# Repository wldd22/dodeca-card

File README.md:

# Dodeca Card

A stylised business card with segmented displays and a capacitive slider.

## Details
PCB made in **KiCad**<br>
Firmware uses **CircuitPython**

**Components**:
- **Seeed Studio XIAO ESP32S3**: Microcontroller
- **MAX7219-HLF-5V**: Display Driver IC
- **0.56 inch 4 Digit 7 Segment Display**: Segmented displays
- **MCMF006FF3002A50**: Through Hole Resistor

**Features**:
- **8 seven-segment digits**, in two sets, connected via a MAX7219 driver
- 8 step **capacitive touch** slider

## About
This project, inspired by [Mitxela's StyloCard](https://mitxela.com/projects/stylocard),
was originally made for week 4 (Display week) of Hack Club's Half Life. I wanted to make
a compact board with stylised graphics on it and a simple display that could show live
values or text updating, like a countdown, an RSS feed, or Github stars.

The touch slider at the bottom of the board acts as a multi-purpose input. It can be used
to scroll through text, select/change options, or adjust values smoothly. It has 8 steps,
corresponding to the 8 digits on the display, meaning it can also be used to individually
target digits on the display.

## Images

### Schematic

### PCB Routing

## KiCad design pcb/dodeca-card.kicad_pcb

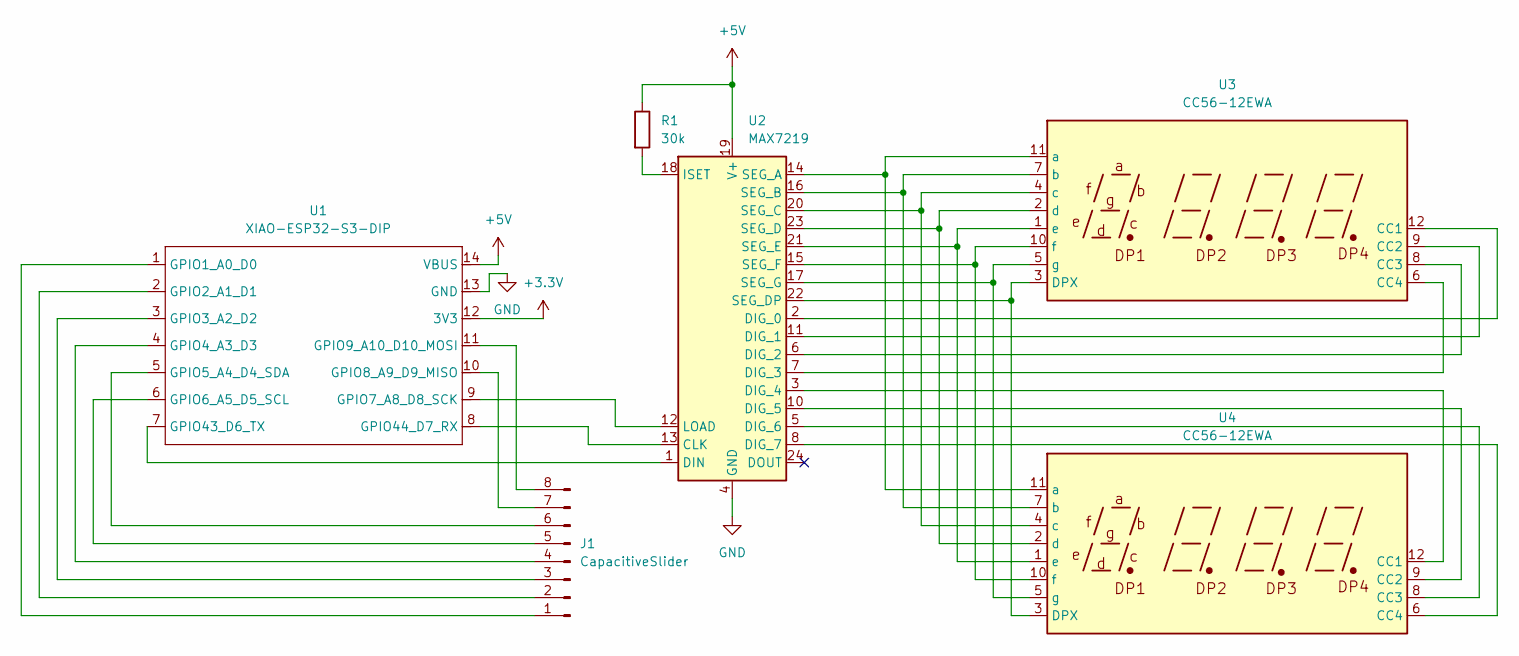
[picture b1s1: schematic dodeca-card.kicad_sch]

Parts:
J1: CapacitiveSlider; TouchSlider-8
R1: 30k; R_Axial_DIN0207_L6.3mm_D2.5mm_P10.16mm_Horizontal
U1: XIAO-ESP32-S3-DIP
U2: MAX7219; DIP-24_W15.24mm
U3, U4: CC56-12EWA; CA56-12EWA

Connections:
+3.3V: U1.12 (3V3)
+5V: R1.1, U1.14 (VBUS), U2.19 (V+)
GND: U1.13 (GND), U2.4 (GND), U2.9 (GND)
unnamed: J1.1, U1.1 (GPIO1_A0_D0)
unnamed: J1.2, U1.2 (GPIO2_A1_D1)
unnamed: J1.3, U1.3 (GPIO3_A2_D2)
unnamed: J1.4, U1.4 (GPIO4_A3_D3)
unnamed: J1.5, U1.6 (GPIO6_A5_D5_SCL)
unnamed: J1.6, U1.5 (GPIO5_A4_D4_SDA)
unnamed: J1.7, U1.10 (GPIO8_A9_D9_MISO)
unnamed: J1.8, U1.11 (GPIO9_A10_D10_MOSI)
unnamed: U1.9 (GPIO7_A8_D8_SCK), U2.12 (LOAD)
unnamed: U1.7 (GPIO43_D6_TX), U2.1 (DIN)
unnamed: U1.8 (GPIO44_D7_RX), U2.13 (CLK)
unnamed: U2.2 (DIG_0), U3.12 (CC1)
unnamed: U2.11 (DIG_1), U3.9 (CC2)
unnamed: U2.6 (DIG_2), U3.8 (CC3)
unnamed: U2.7 (DIG_3), U3.6 (CC4)
unnamed: U2.3 (DIG_4), U4.12 (CC1)
unnamed: U2.10 (DIG_5), U4.9 (CC2)
unnamed: U2.5 (DIG_6), U4.8 (CC3)
unnamed: U2.8 (DIG_7), U4.6 (CC4)
unnamed: R1.2, U2.18 (ISET)
unnamed: U2.14 (SEG_A), U3.11 (a), U4.11 (a)
unnamed: U2.16 (SEG_B), U3.7 (b), U4.7 (b)
unnamed: U2.20 (SEG_C), U3.4 (c), U4.4 (c)
unnamed: U2.23 (SEG_D), U3.2 (d), U4.2 (d)
unnamed: U2.22 (SEG_DP), U3.3 (DPX), U4.3 (DPX)
unnamed: U2.21 (SEG_E), U3.1 (e), U4.1 (e)
unnamed: U2.15 (SEG_F), U3.10 (f), U4.10 (f)
unnamed: U2.17 (SEG_G), U3.5 (g), U4.5 (g)

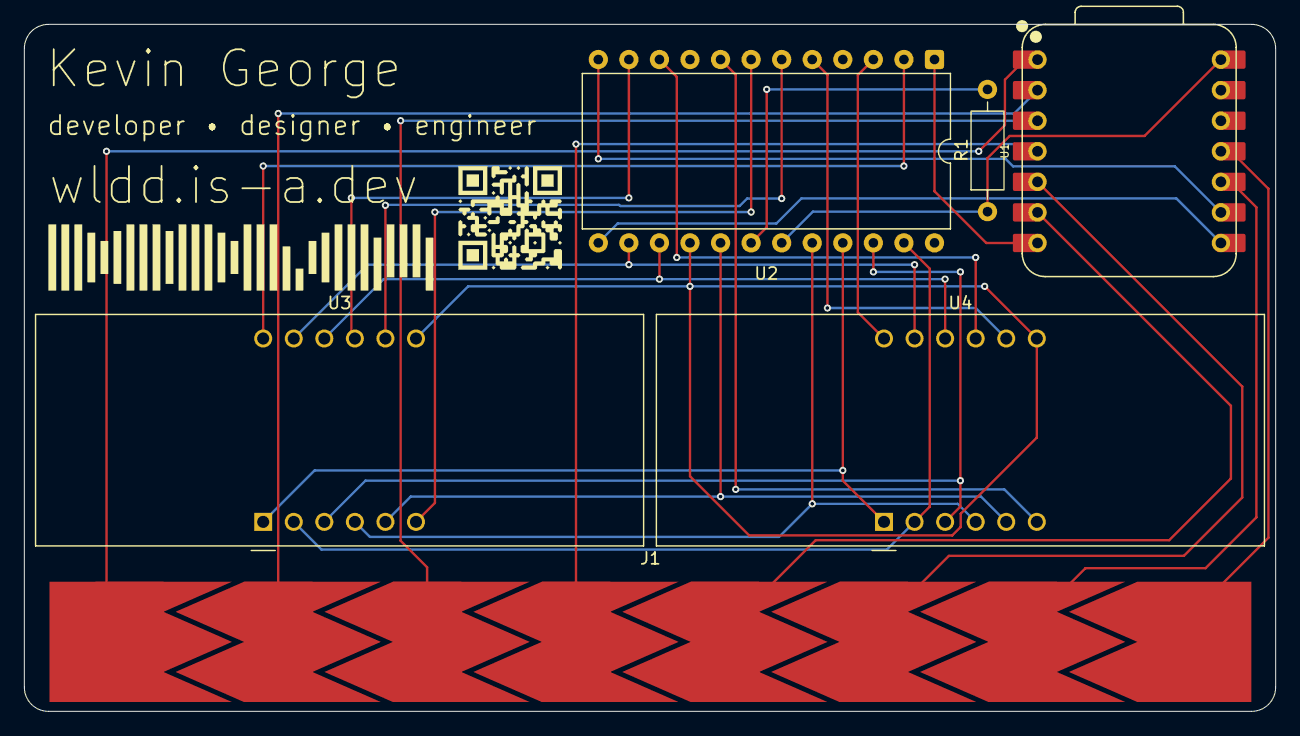
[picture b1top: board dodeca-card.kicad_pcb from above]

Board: 2 copper layers, 104.0 x 57.1 mm, 6 parts (0 on the bottom side), 30 nets.
